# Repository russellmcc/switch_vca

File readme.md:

This is an experimental design for a switched-mode VCA for eurorack format modular synthesizers.  It's intended to be a cheap replacement for a traditional OTA-based VCA.

This work is licensed under a [Creative Commons Attribution-ShareAlike 3.0 Unported License.](http://creativecommons.org/licenses/by-sa/3.0/deed.en_US)

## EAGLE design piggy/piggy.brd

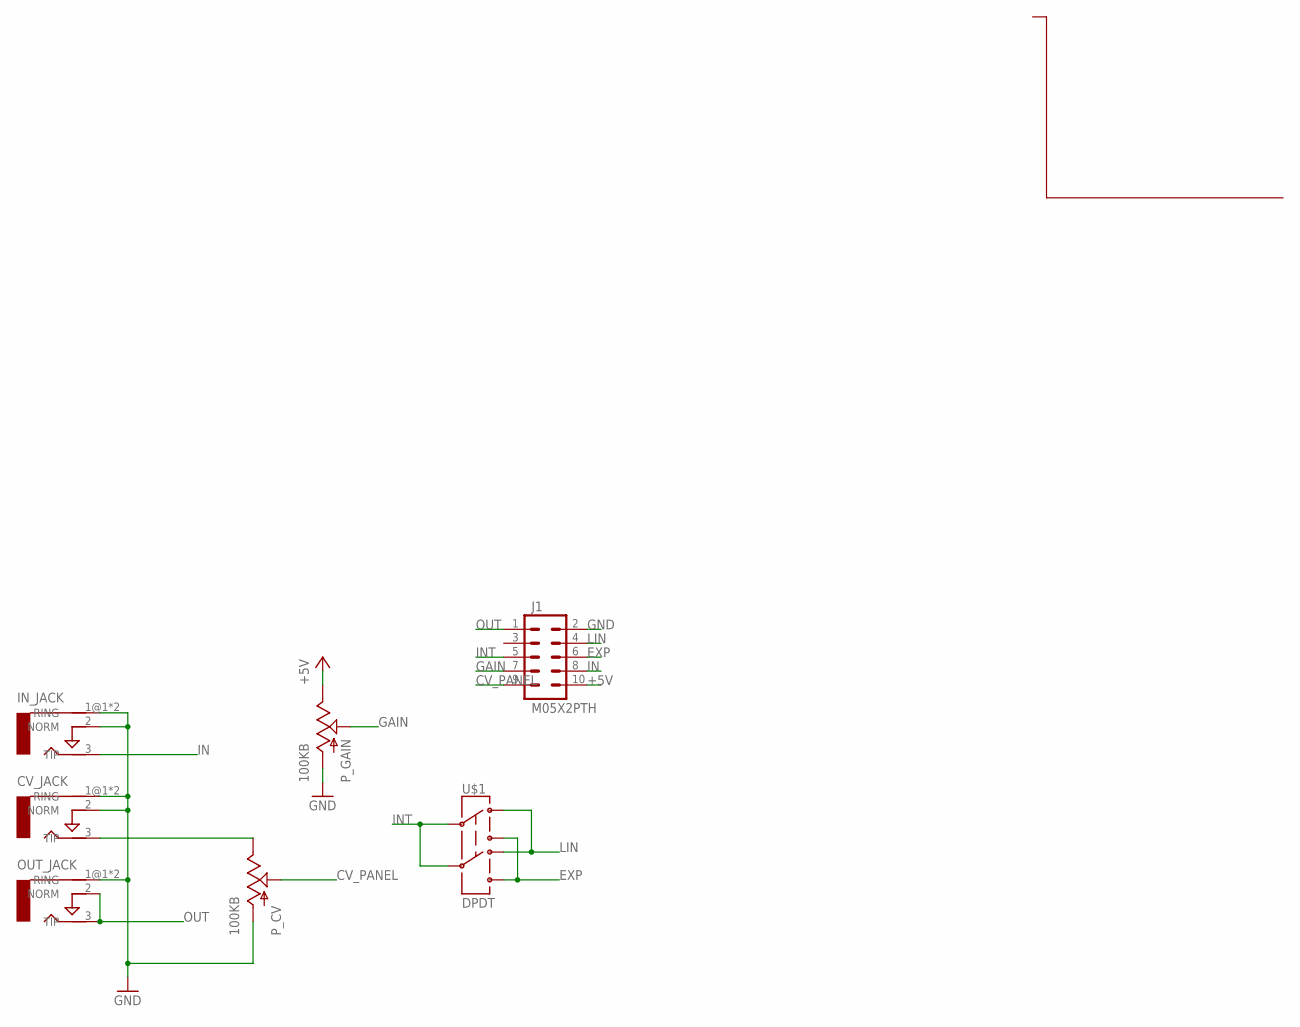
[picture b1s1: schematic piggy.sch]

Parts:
CV_JACK: AUDIO-JACKERTHENVAR; ERTHENVAR-JACK
IN_JACK: AUDIO-JACKERTHENVAR; ERTHENVAR-JACK
J1: M05X2PTH; AVR_ICSP
OUT_JACK: AUDIO-JACKERTHENVAR; ERTHENVAR-JACK
P_CV: 100KB; PDB12
P_GAIN: 100KB; PDB12
U$1: DPDT; MOUNTAIN_10SL005

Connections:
+5V: J1.10, P_GAIN.3 (E)
CV_PANEL: J1.9, P_CV.2 (S)
EXP: J1.6, U$1.Y1, U$1.Y2
GAIN: J1.7, P_GAIN.2 (S)
GND: CV_JACK.1@1 (RING), CV_JACK.1@2 (RING), CV_JACK.2 (NORM), IN_JACK.1@1 (RING), IN_JACK.1@2 (RING), IN_JACK.2 (NORM), J1.2, OUT_JACK.1@1 (RING), OUT_JACK.1@2 (RING), P_CV.1 (A), P_GAIN.1 (A)
IN: IN_JACK.3 (TIP), J1.8
INT: J1.5, U$1.C1, U$1.C2
LIN: J1.4, U$1.X1, U$1.X2
unnamed: CV_JACK.3 (TIP), P_CV.3 (E)
OUT: J1.1, OUT_JACK.2 (NORM), OUT_JACK.3 (TIP)

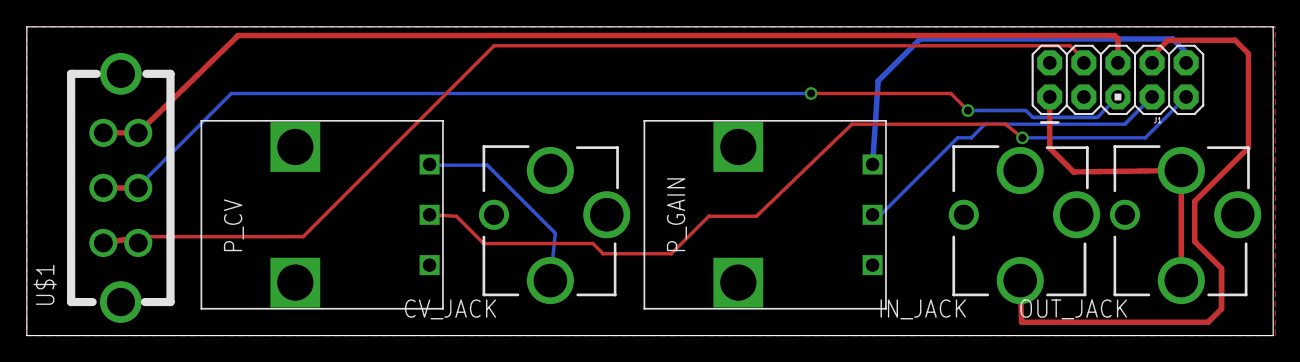
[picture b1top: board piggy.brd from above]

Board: 2 copper layers, 92.8 x 23.0 mm, 7 parts (0 on the bottom side), 10 nets.

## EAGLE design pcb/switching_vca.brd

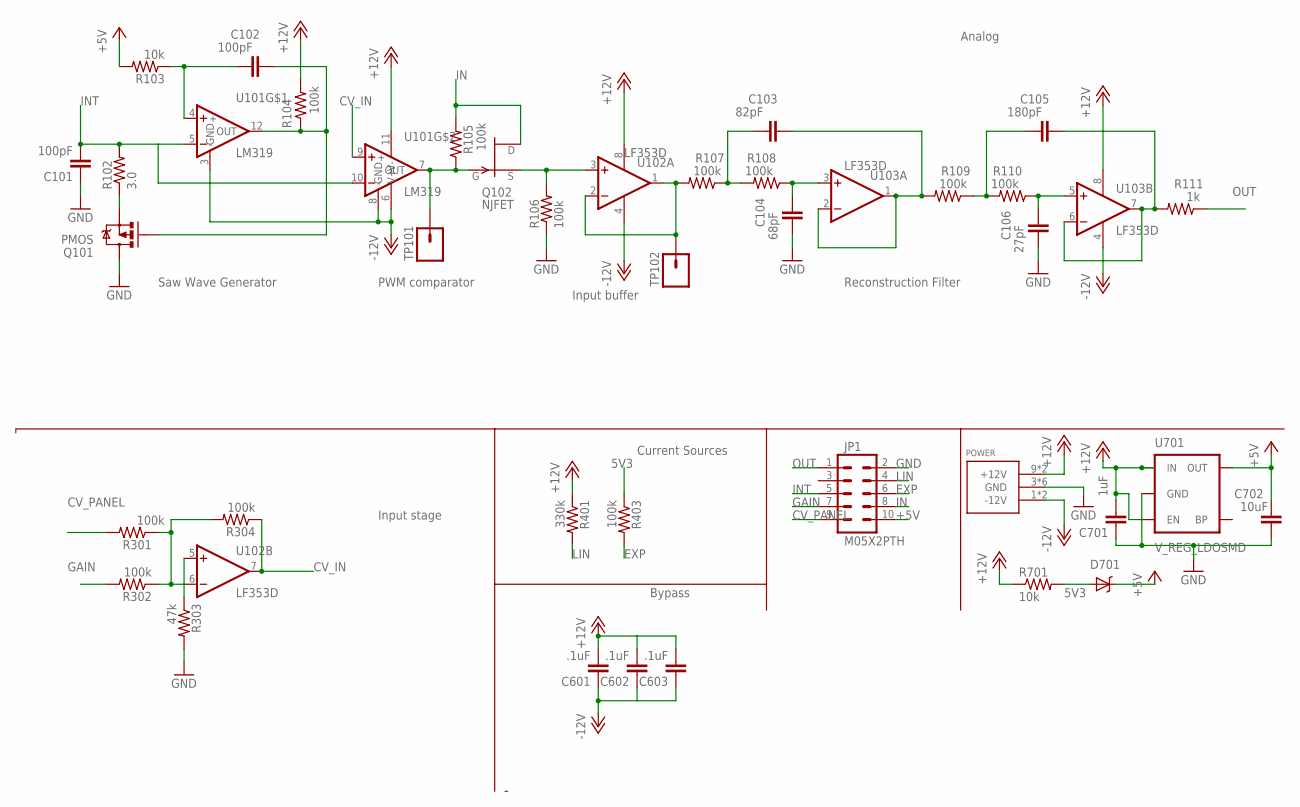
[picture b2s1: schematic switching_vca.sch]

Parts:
C101, C102: 100pF; 0603-CAP
C103: 82pF; 0603-CAP
C104: 68pF; 0603-CAP
C105: 180pF; 0603-CAP
C106: 27pF; 0603-CAP
C601, C602, C603: .1uF; 0603-CAP
C701: 1uF; 0805
C702: 10uF; 1206
D701: DIODE-SCHOTTKY; SOD-323
JP1: M05X2PTH; AVR_ICSP
POWER: POWER_SIMPLE16; POWER_16
Q101: PMOS; SOT23-3
Q102: NJFET; SOT23
R102: 3.0; 0603-RES
R103, R701: 10k; 0603-RES
R104, R105, R106, R107, R108, R109, R110, R301, R302, R304, R403: 100k; 0603-RES
R111: 1k; 0603-RES
R303: 47k; 0603-RES
R401: 330k; 0603-RES
TP101, TP102: M01PTH; 1X01
U101: LM319; SOP-14
U102, U103: LF353D; SO08
U701: V_REG_LDOSMD; SOT23-5

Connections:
5V3: D701.1 (A), R403.1, R701.2
+5V: C702.1, D701.2 (C), JP1.10, R103.2, U701.5 (OUT)
+12V: C601.2, C602.2, C603.2, C701.2, POWER.9 (+12V), POWER.10 (+12V), R104.2, R401.1, R701.1, U101.11 (V+), U102.8 (V+), U103.8 (V+), U701.1 (IN), U701.3 (EN)
-12V: C601.1, C602.1, C603.1, POWER.1 (-12V), POWER.2 (-12V), U101.3 (GND), U101.6 (V-), U101.8 (GND), U102.4 (V-), U103.4 (V-)
CV_IN: R304.1, U102.7 (OUT)
CV_PANEL: JP1.9, R301.2
EXP: JP1.6, R403.2
GAIN: JP1.7, R302.2
GND: C101.1, C104.2, C106.2, C701.1, C702.2, JP1.2, POWER.3 (GND), POWER.4 (GND), POWER.5 (GND), POWER.6 (GND), POWER.7 (GND), POWER.8 (GND), Q101.3 (D), R106.1, R303.2, U701.2 (GND)
IN: JP1.8, Q102.1 (D), R105.2
INT: C101.2, JP1.5, R102.2, U101.5 (-), U101.10 (-)
LIN: JP1.4, R401.2
N$: C102.1, Q101.1 (G), R104.1, U101.12 (OUT)
unnamed: Q101.2 (S), R102.1
unnamed: Q102.3 (G), R105.1, TP101.1, U101.7 (OUT)
unnamed: C102.2, R103.1, U101.4 (+)
unnamed: C103.1, R109.2, U103.1 (OUT), U103.2 (-IN)
unnamed: Q102.2 (S), R106.2, U102.3 (+IN)
unnamed: C103.2, R107.1, R108.2
unnamed: C104.1, R108.1, U103.3 (+IN)
unnamed: R303.1, U102.5 (+IN)
unnamed: C105.2, R109.1, R110.2
unnamed: C106.1, R110.1, U103.5 (+IN)
unnamed: C105.1, R111.2, U103.6 (-IN), U103.7 (OUT)
unnamed: R107.2, TP102.1, U102.1 (OUT), U102.2 (-IN)
OUT: JP1.1, R111.1
R301: R301.1, R302.1, R304.2, U102.6 (-IN)

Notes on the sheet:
Saw Wave Generator
PWM comparator
Reconstruction Filter
Analog
Input stage
Current Sources
Bypass
Input buffer

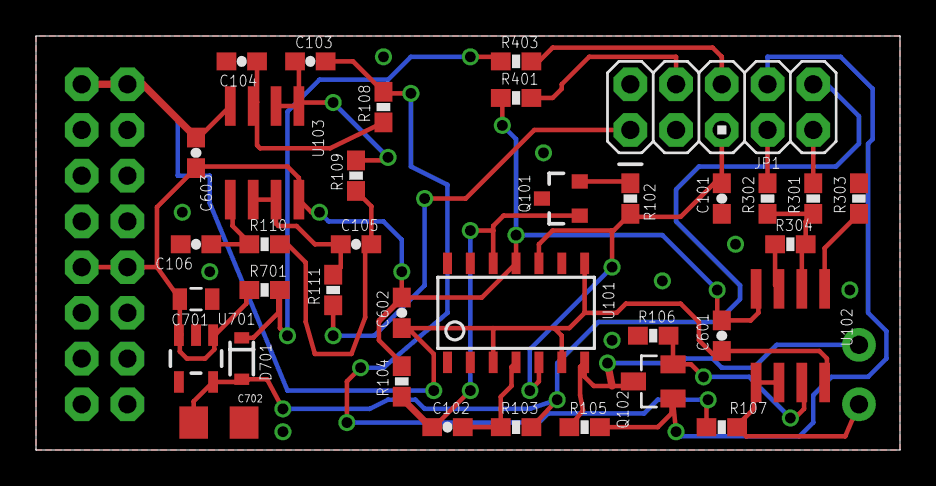
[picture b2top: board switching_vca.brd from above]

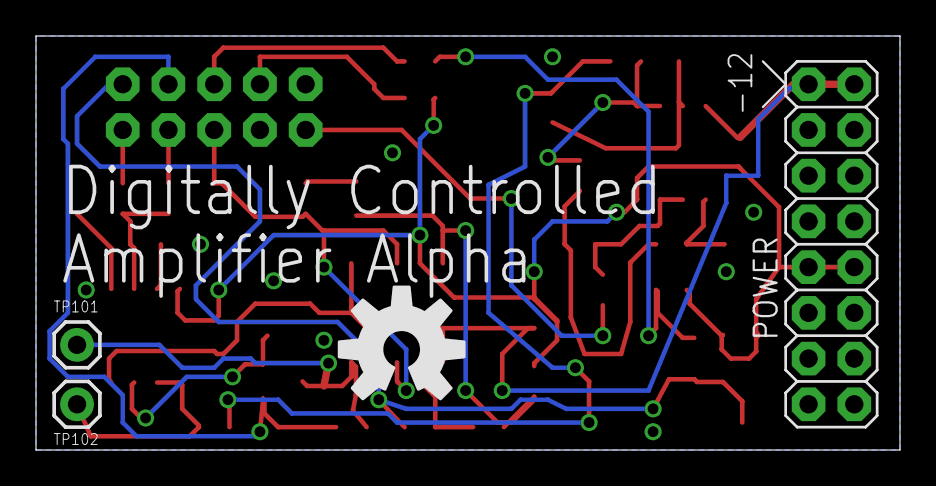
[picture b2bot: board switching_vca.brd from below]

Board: 2 copper layers, 48.0 x 23.0 mm, 40 parts (4 on the bottom side), 27 nets.

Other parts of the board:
U$1: OSHW-LOGO-L

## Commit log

2012-12-30 initial
2013-01-03 added some simulations
2013-01-06 found a fast comparator so remove the level conversion stage of the switch simulation
2013-01-07 First attempt at schem (footprints not specced), initial BOM
2013-01-10 added shitty board, made mouser bom
2013-01-11 Routed the board with a travesty of VIAs
2013-01-11 Added a piggy back board
2013-01-11 aligned jacks to pot origin
2013-01-11 added .gitignore
2013-01-17 Laid out panel.
2013-01-27 hole placement
2013-02-07 added test point for PWM comparator output
2013-02-16 fixed footprint/front panel

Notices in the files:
parts and their libraries:
SparkFun: Licensing: CC v3.0 Share-Alike You are welcome to use this library for commercial purposes.
